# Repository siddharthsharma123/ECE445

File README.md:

# ECE445
UIUC - ECE 445 Senior Design

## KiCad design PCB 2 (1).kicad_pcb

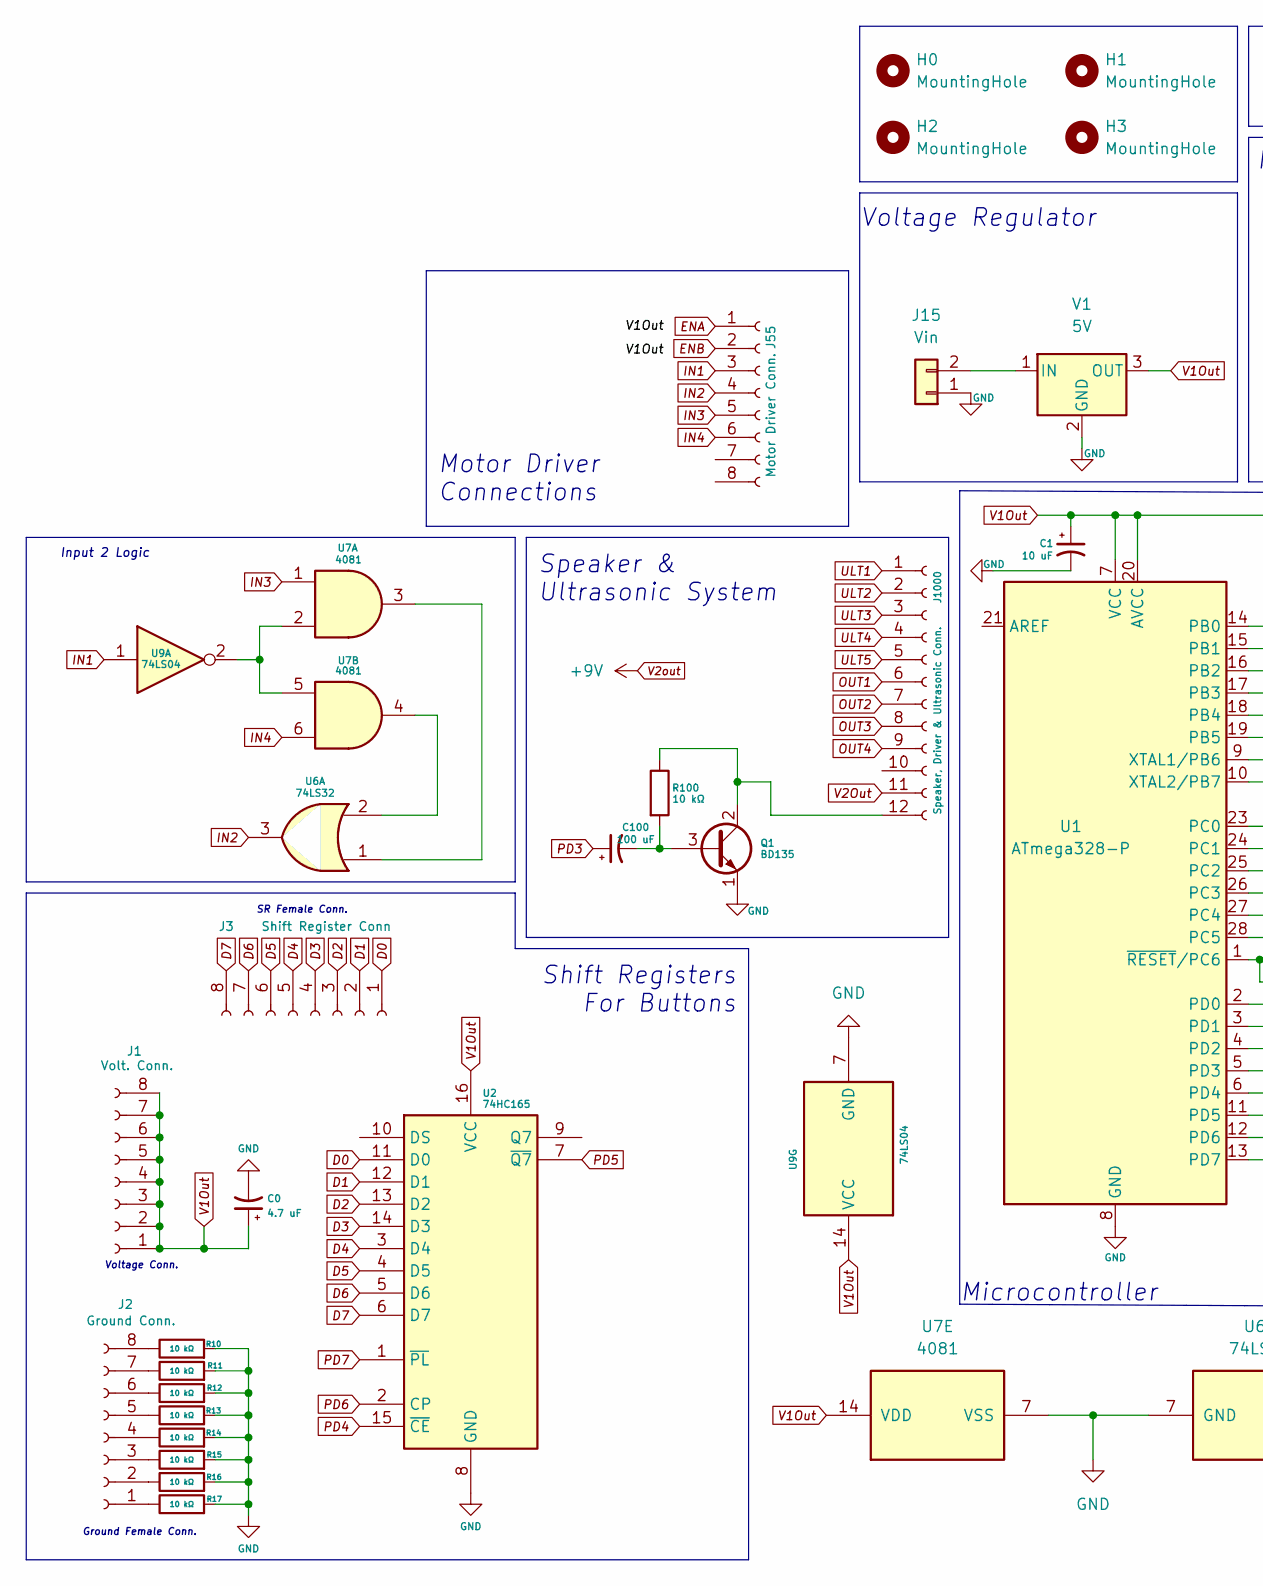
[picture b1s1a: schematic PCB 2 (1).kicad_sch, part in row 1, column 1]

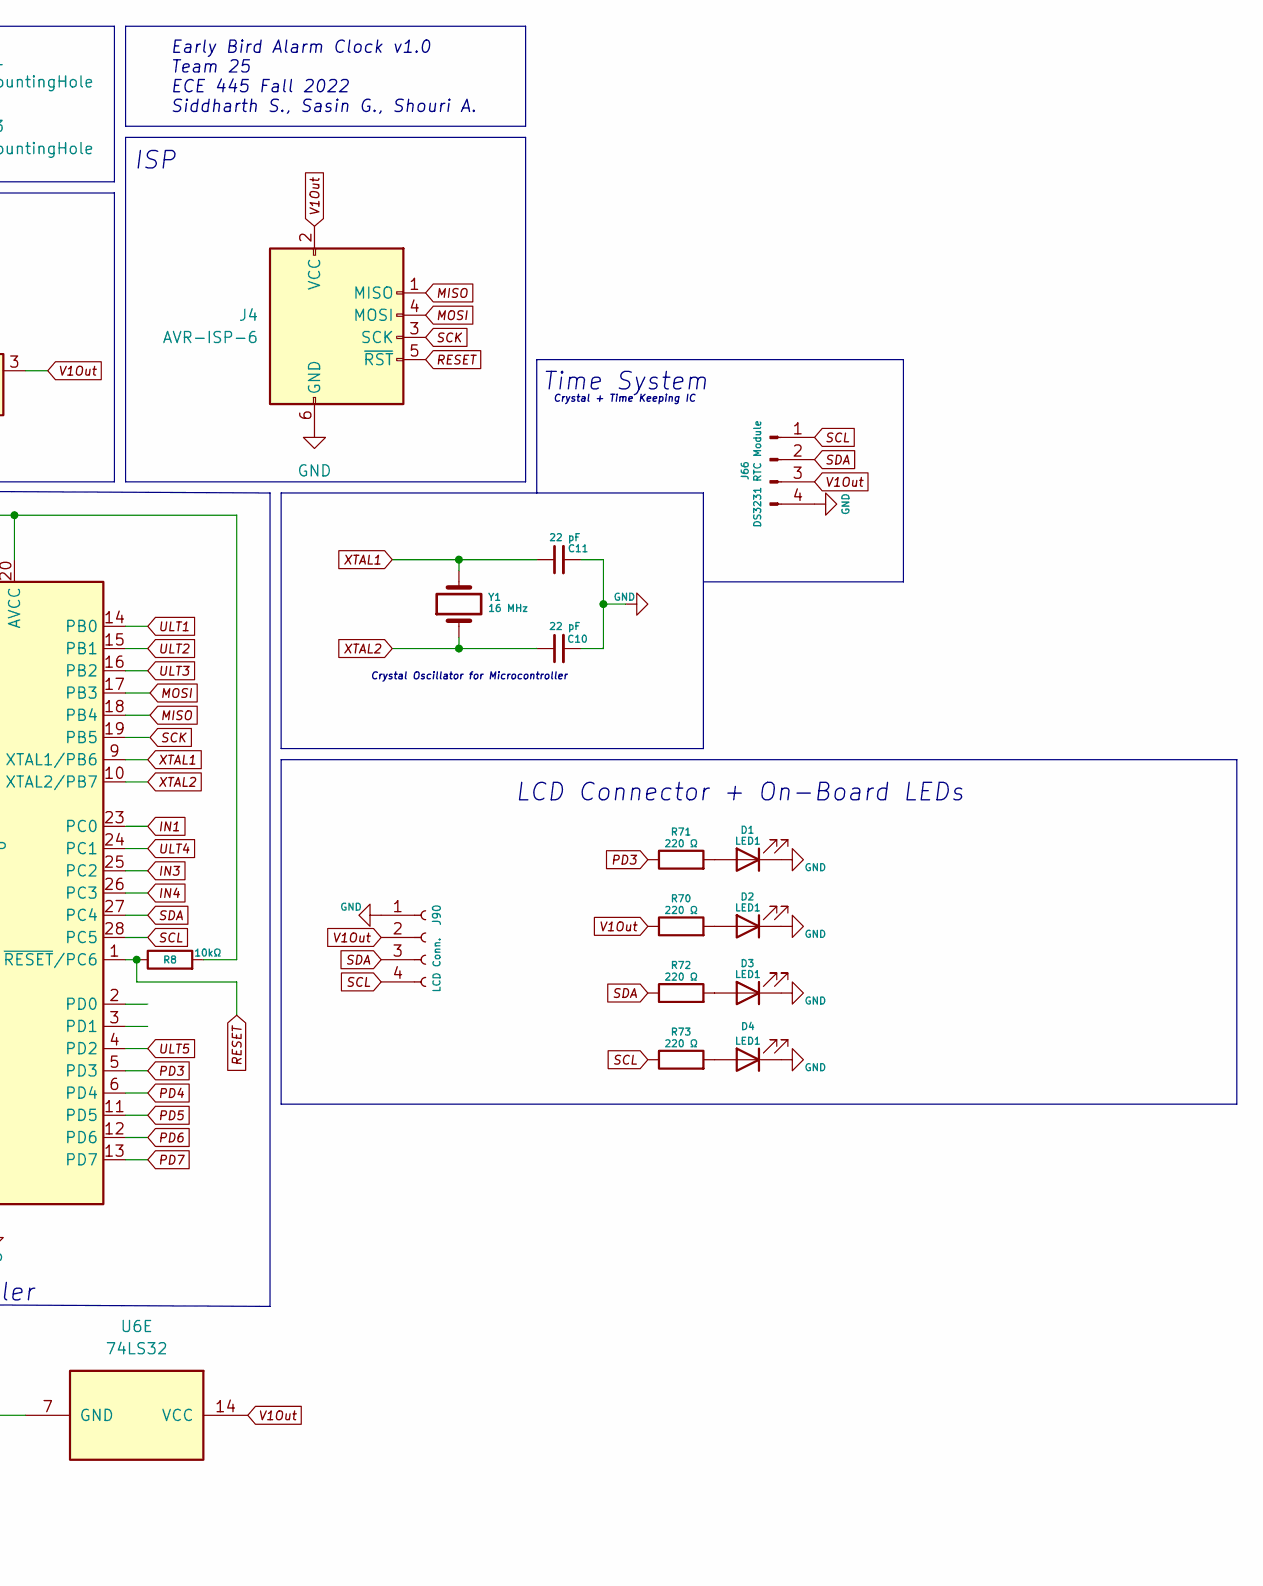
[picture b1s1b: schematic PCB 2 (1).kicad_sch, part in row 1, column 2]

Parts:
C0: 4.7 uF; CP_Radial_D5.0mm_P2.50mm
C1: 10 uF; CP_Radial_D5.0mm_P2.50mm
C10, C11: 22 pF; CP_Radial_D5.0mm_P2.50mm
C100: 100 uF; CP_Radial_D5.0mm_P2.50mm
D1, D2, D3, D4: LED1; LED_D1.8mm_W1.8mm_H2.4mm_Horizontal_O1.27mm_Z1.6mm
H0, H1, H2, H3: MountingHole; MountingHole_3.2mm_M3
J1: Volt. Conn.; PinHeader_1x08_P2.54mm_Vertical
J2: Ground Conn.; PinHeader_1x08_P2.54mm_Vertical
J3: Shift Register Conn; PinHeader_1x08_P2.54mm_Vertical
J4: AVR-ISP-6; IDC-Header_2x03_P2.54mm_Vertical
J15: Vin; Molex_CLIK-Mate_502382-0270_1x02-1MP_P1.25mm_Vertical
J55: Motor Driver Conn.; PinHeader_1x08_P2.54mm_Vertical
J66: DS3231 RTC Module; PinSocket_1x04_P2.54mm_Vertical
J90: LCD Conn.; PinHeader_1x04_P2.54mm_Vertical
J1000: Speaker, Driver & Ultrasonic Conn.; PinHeader_1x12_P2.54mm_Vertical
Q1: BD135; TO-126-3_Vertical
R8: 10kΩ; R_Axial_DIN0204_L3.6mm_D1.6mm_P7.62mm_Horizontal
R10, R11, R12, R13, R14, R15, R16, R17, R100: 10 kΩ; R_Axial_DIN0204_L3.6mm_D1.6mm_P7.62mm_Horizontal
R70, R71, R72, R73: 220 Ω; R_Axial_DIN0204_L3.6mm_D1.6mm_P7.62mm_Horizontal
U1: ATmega328-P; DIP-28_W7.62mm
U2: 74HC165; DIP794W45P254L1969H508Q16
U6: 74LS32; DIP794W45P254L1969H508Q14
U7: 4081; DIP794W45P254L1969H508Q14
U9: 74LS04; DIP794W46P254L1969H533Q14
V1: 5V; TO254P1054X470X2600-3
Y1: 16 MHz; Crystal_HC49-U_Vertical

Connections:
D0: J3.1, U2.11 (D0)
D1: J3.2, U2.12 (D1)
D2: J3.3, U2.13 (D2)
D3: J3.4, U2.14 (D3)
D4: J3.5, U2.3 (D4)
D5: J3.6, U2.4 (D5)
D6: J3.7, U2.5 (D6)
D7: J3.8, U2.6 (D7)
ENA: J55.1
ENB: J55.2
GND: C0.2, C1.2, C10.2, C11.2, D1.1 (K), D2.1 (K), D3.1 (K), D4.1 (K), J4.6 (GND), J15.1, J66.4, J90.1, Q1.1 (E), R10.2, R11.2, R12.2, R13.2, R14.2, R15.2, R16.2, R17.2, U1.8 (GND), U1.22 (GND), U2.8 (GND), U6.7 (GND), U7.7 (VSS), U9.7 (GND), V1.2 (GND)
IN1: J55.3, U1.23 (PC0), U9.1
IN2: J55.4, U6.3
IN3: J55.5, U1.25 (PC2), U7.1
IN4: J55.6, U1.26 (PC3), U7.6
MISO: J4.1 (MISO), U1.18 (PB4)
MOSI: J4.4 (MOSI), U1.17 (PB3)
unnamed: C100.2, Q1.3 (B), R100.2
unnamed: D1.2 (A), R71.2
unnamed: D2.2 (A), R70.2
unnamed: D3.2 (A), R72.2
unnamed: D4.2 (A), R73.2
unnamed: J2.1, R17.1
unnamed: J2.2, R16.1
unnamed: J2.3, R15.1
unnamed: J2.4, R14.1
unnamed: J2.5, R13.1
unnamed: J2.6, R12.1
unnamed: J2.7, R11.1
unnamed: J2.8, R10.1
unnamed: J15.2, V1.1 (IN)
unnamed: J1000.12, Q1.2 (C), R100.1
unnamed: U6.1, U7.3
unnamed: U6.2, U7.4
unnamed: U7.2, U7.5, U9.2
OUT1: J1000.6
OUT2: J1000.7
OUT3: J1000.8
OUT4: J1000.9
PD3: C100.1, R71.1, U1.5 (PD3)
PD4: U1.6 (PD4), U2.15 (~CE)
PD5: U1.11 (PD5), U2.7 (~Q7)
PD6: U1.12 (PD6), U2.2 (CP)
PD7: U1.13 (PD7), U2.1 (~PL)
RESET: J4.5 (~RST), R8.1, U1.1 (~RESET/PC6)
SCK: J4.3 (SCK), U1.19 (PB5)
SCL: J66.1, J90.4, R73.1, U1.28 (PC5)
SDA: J66.2, J90.3, R72.1, U1.27 (PC4)
ULT1: J1000.1, U1.14 (PB0)
ULT2: J1000.2, U1.15 (PB1)
ULT3: J1000.3, U1.16 (PB2)
ULT4: J1000.4, U1.24 (PC1)
ULT5: J1000.5, U1.4 (PD2)
V1Out: C0.1, C1.1, J1.1, J1.2, J1.3, J1.4, J1.5, J1.6, J1.7, J1.8, J4.2 (VCC), J66.3, J90.2, R8.2, R70.1, U1.7 (VCC), U1.20 (AVCC), U2.16 (VCC), U6.14 (VCC), U7.14 (VDD), U9.14 (VCC), V1.3 (OUT)
V2Out: J1000.11
XTAL1: C11.1, U1.9 (XTAL1/PB6), Y1.2
XTAL2: C10.1, U1.10 (XTAL2/PB7), Y1.1

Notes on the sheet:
Shift Registers For Buttons
Crystal Oscillator for Microcontroller
LCD Connector + On-Board LEDs
Voltage Regulator
ISP
Crystal + Time Keeping IC
Speaker & Ultrasonic System
Input 2 Logic
Time System
Voltage Conn.
SR Female Conn.
Microcontroller
Motor Driver Connections
Early Bird Alarm Clock v1.0 Team 25 ECE 445 Fall 2022 Siddharth S., Sasin G., Shouri A.
Ground Female Conn.

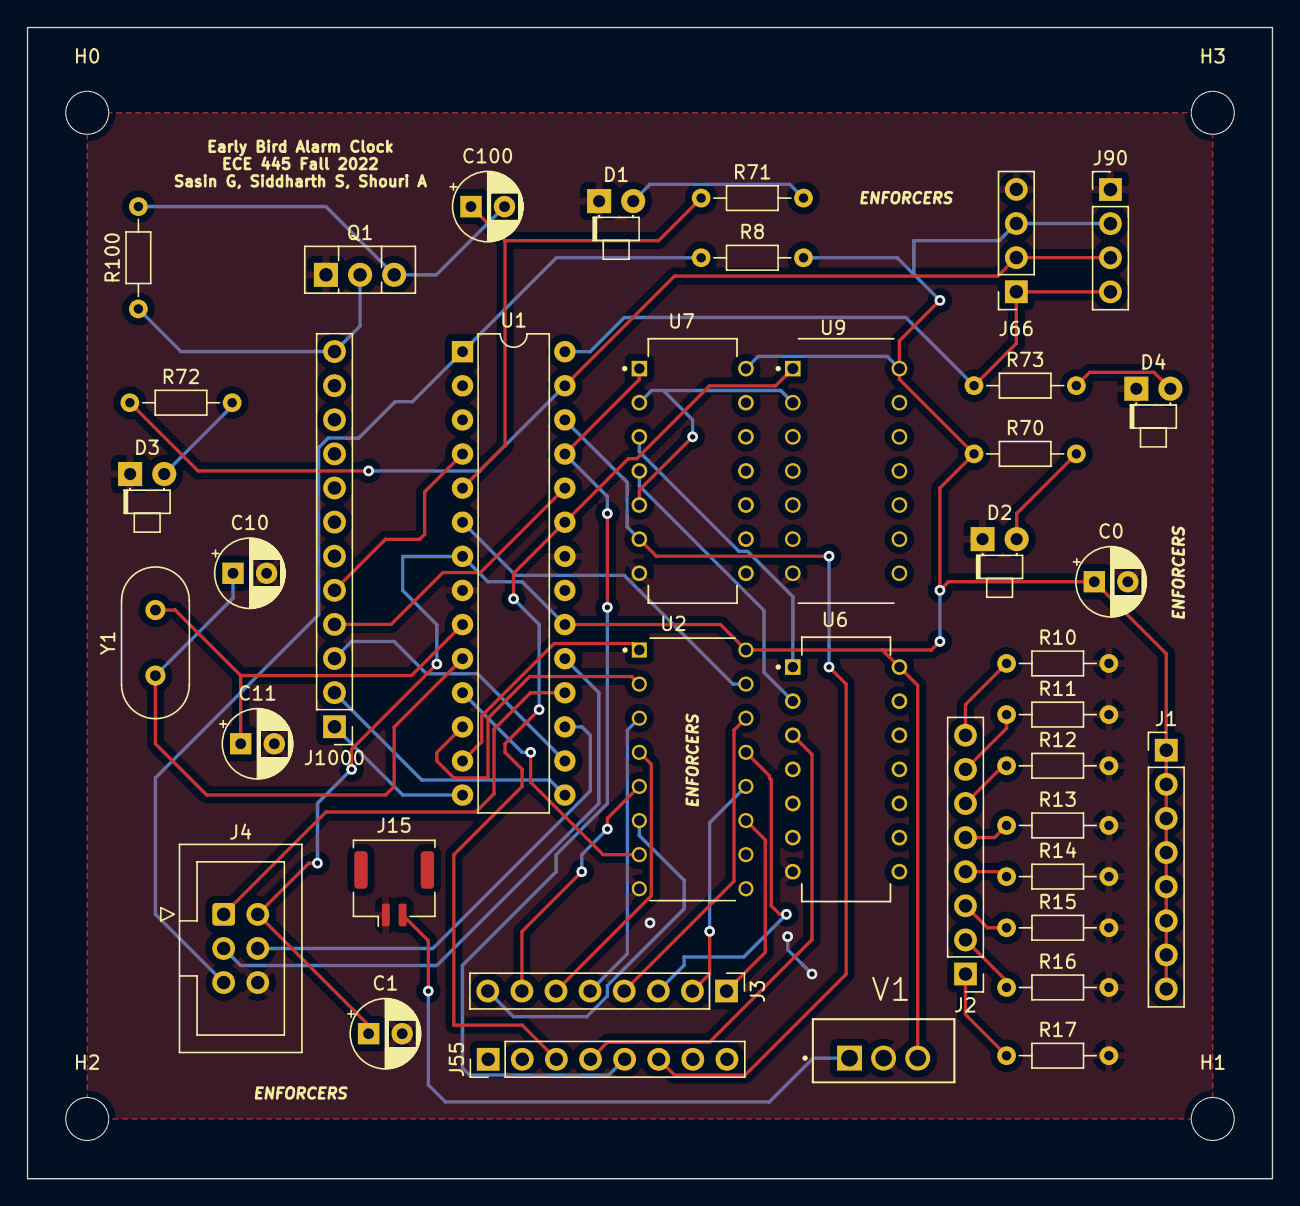
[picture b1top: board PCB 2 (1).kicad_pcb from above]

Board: 2 copper layers, 92.7 x 85.7 mm, 44 parts (0 on the bottom side), 50 nets.

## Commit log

2022-11-05 Add motor driver code
2022-11-05 updating ino file for simple motor driver test
2022-11-05 updating motors.cpp
2022-11-06 Add Ultrasonic Sonic Sensor module
2022-11-06 Fix include statements
2022-11-09 Add filtering to ultrasonics
2022-11-09 Finish filtering and delete useless files
2022-11-11 Create speaker and buttons files
2022-11-11 Add speaker class
2022-11-11 adding obstacle avoidance code
2022-11-15 Add Alarm Clock, fix speaker bugs, add buttons test code
2022-11-18 Change button vector, switch to buzzer, add alarm state
2022-12-07 added kicad files
